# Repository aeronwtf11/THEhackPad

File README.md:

# TH3 HACKP4D

My hackpad for Hack Club. 4 keys, 4 RGB LEDs and a tiny 0.91" OLED, running on a Seeed XIAO RP2040 with KMK.

The whole build, day by day, is in my [journal](journal.md).

Press a key and the LED next to it lights up, and the screen shows the song that's playing on my PC (title and artist). I like seeing the tech, so the case has windows: you can see the XIAO, the LEDs, the Hack Club flag on the PCB and the screen.

## What's in it

- Seeed XIAO RP2040, soldered flat on the front (top right corner)
- 4x MX switches (Gateron Green) with blank smokey keycaps
- 4x SK6812MINI-E LEDs, chained on D0
- 0.91" 128x32 SSD1306 OLED over I2C
- 3D printed case, 73.3 x 100.8 x 17 mm, 3x M3 screws into heat set inserts

All parts with links and prices are in [BOM.csv](BOM.csv).

## PCB

52.5 x 80 mm, 2 layers. The LEDs sit in cut-outs in the board so you can see them through the case.

## Schematic

| | Pin |
|---|---|
| SW1 / SW2 / SW3 / SW4 | D10 / D9 / D8 / D7 (other side to GND) |
| LED data | D0 |
| OLED SDA / SCL | D4 / D5 (address 0x3C) |

## Folders

- `journal.md` my build log
- `PCB/` KiCad project
- `production/` gerbers, the zip is what goes to JLCPCB
- `case/` FreeCAD file, STEP and the STL files for printing
- `firmware/` KMK firmware
- `host/` small script for the PC that sends the song to the screen
- `assets/` logos

## Firmware

1. Flash CircuitPython for the XIAO RP2040 (hold BOOT, plug in, drop the .uf2 on the drive).
2. Copy the `kmk` folder from [kmk_firmware](https://github.com/KMKfw/kmk_firmware) onto CIRCUITPY.
3. Put `neopixel`, `adafruit_displayio_ssd1306` and `adafruit_display_text` from the Adafruit CircuitPython bundle into `lib/`.
4. Copy `firmware/main.py` and `firmware/boot.py` onto the drive, then unplug it and plug it back in.

Right now the keys are play/pause, volume down, volume up and mute. Change the `KEYS` list at the top of `main.py` if you want something else. If the screen shows everything upside down, set `FLIP_SCREEN = True`.

### Song on the screen

The hackpad can't know what's playing by itself, so `host/nowplaying.py` tells it. It uses `playerctl` (Linux), so Spotify, the browser, mpv and so on all work.

```
python3 host/nowplaying.py
```

Leave it running. It finds the hackpad on its own and shows the song while something is playing. Paused = empty screen.

---

wtfnorax productions

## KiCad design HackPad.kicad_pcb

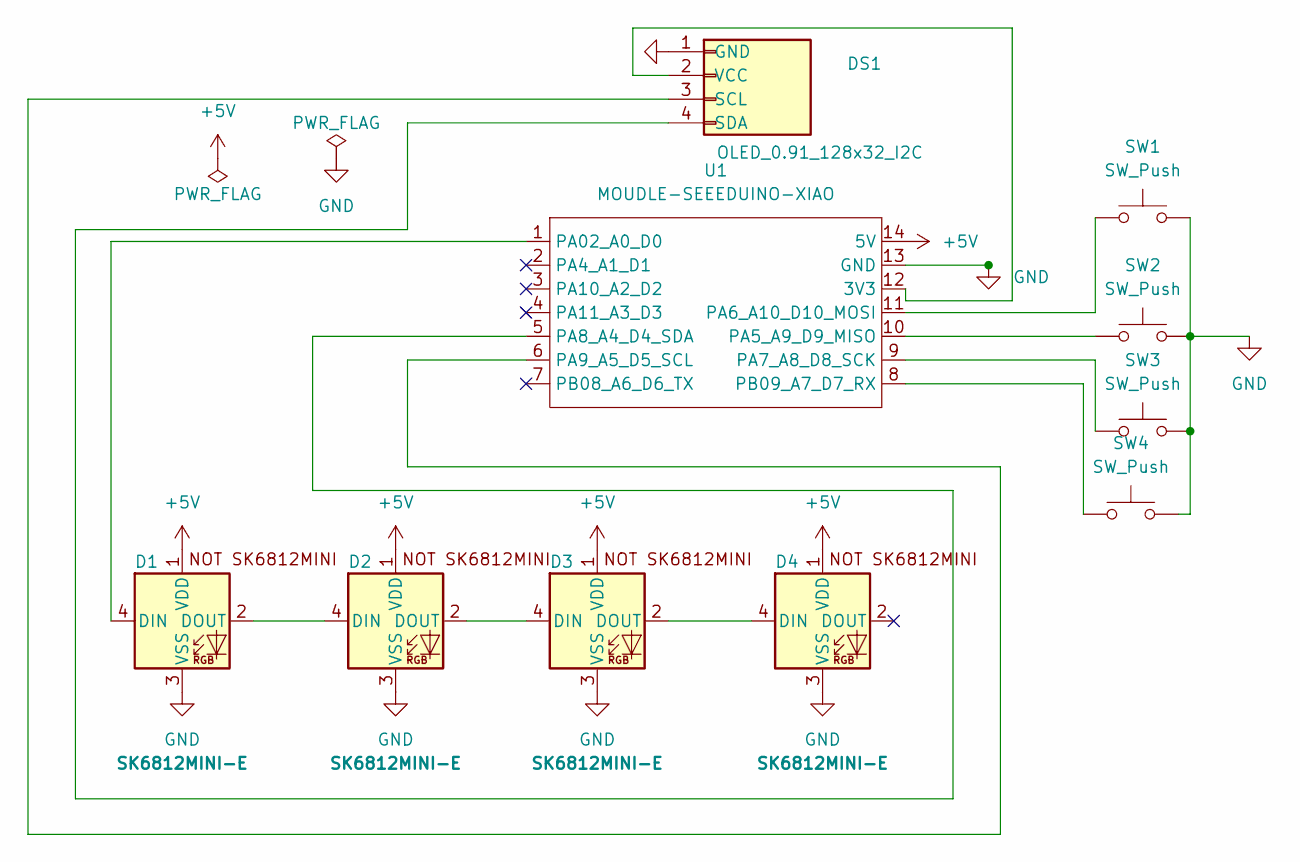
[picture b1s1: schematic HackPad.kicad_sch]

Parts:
D1, D2, D3, D4: SK6812MINI-E; SK6812MINI-E_fixed
DS1: OLED_0.91_128x32_I2C
SW1, SW2, SW3, SW4: SW_Push; SW_Cherry_MX_1.00u_PCB
U1: MOUDLE-SEEEDUINO-XIAO; XIAO-Generic-Hybrid-14P-2.54-21X17.8MM

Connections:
+5V: D1.1 (VDD), D2.1 (VDD), D3.1 (VDD), D4.1 (VDD), U1.14 (5V)
GND: D1.3 (VSS), D2.3 (VSS), D3.3 (VSS), D4.3 (VSS), DS1.1 (GND), SW1.2, SW2.2, SW3.2, SW4.2, U1.13 (GND)
unnamed: D1.4 (DIN), U1.1 (PA02_A0_D0)
unnamed: D1.2 (DOUT), D2.4 (DIN)
unnamed: D2.2 (DOUT), D3.4 (DIN)
unnamed: D3.2 (DOUT), D4.4 (DIN)
unnamed: DS1.3 (SCL), U1.6 (PA9_A5_D5_SCL)
unnamed: DS1.4 (SDA), U1.5 (PA8_A4_D4_SDA)
unnamed: DS1.2 (VCC), U1.12 (3V3)
unnamed: SW2.1, U1.10 (PA5_A9_D9_MISO)
unnamed: SW1.1, U1.11 (PA6_A10_D10_MOSI)
unnamed: SW3.1, U1.9 (PA7_A8_D8_SCK)
unnamed: SW4.1, U1.8 (PB09_A7_D7_RX)

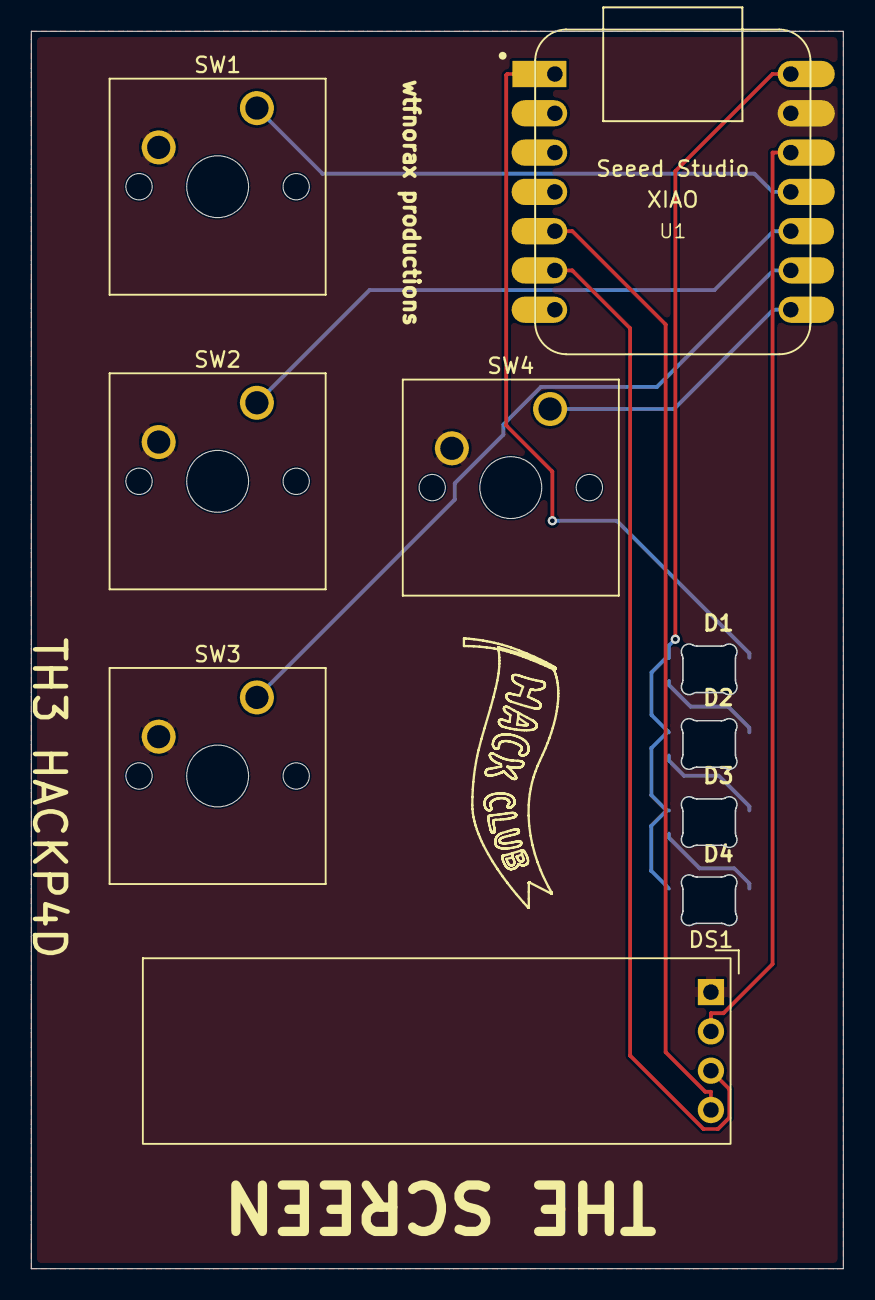
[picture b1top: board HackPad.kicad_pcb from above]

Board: 2 copper layers, 52.5 x 80.0 mm, 10 parts (0 on the bottom side), 13 nets.
